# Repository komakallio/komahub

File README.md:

KomaHub Remote Power Switch and Sensor Platform
===============================================

Contents
--------

**EDA** - schematics and board layout, made in Eagle

**case** - STL files for a 3D-printed case

**software** - KomaHub control software

**firmware** - Firmware code

**tools** - tools for operating the KomaHub

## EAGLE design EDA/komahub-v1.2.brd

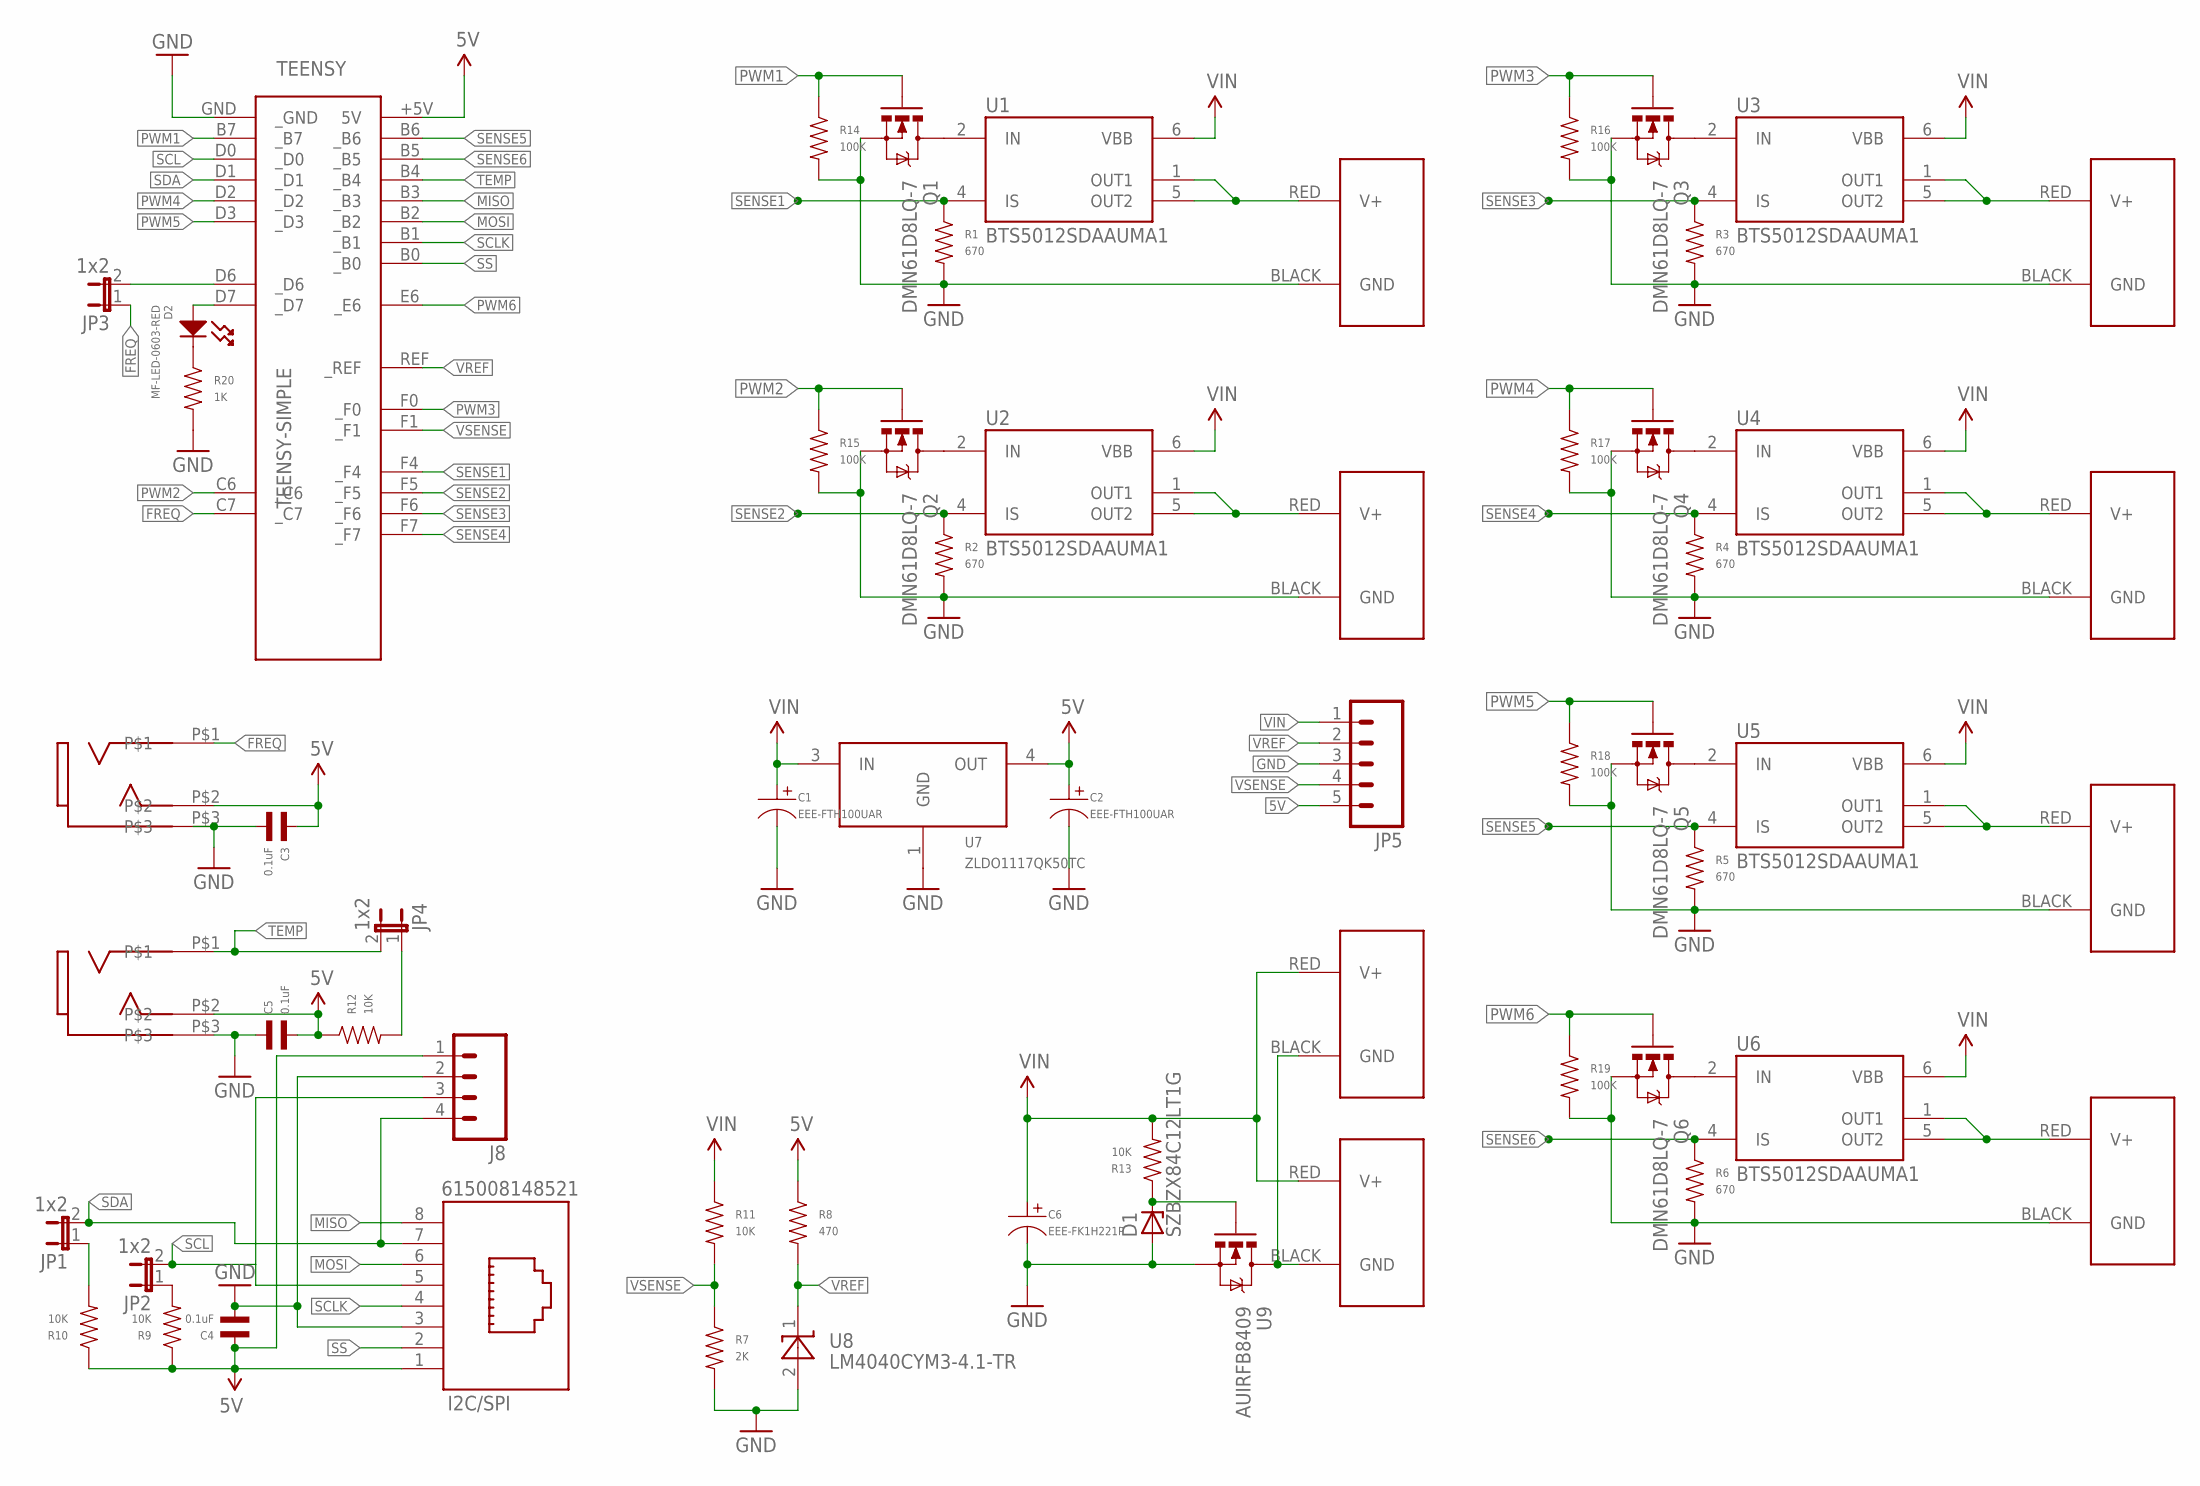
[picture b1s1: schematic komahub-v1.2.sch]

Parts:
C1, C2: EEE-FTH100UAR; CP4MM; MPN MF-CAP-4MM-10uF
C3, C4, C5: 0.1uF; C0603
C6: EEE-FK1H221P; CP10MM; MPN EEE-FT1H221AP
D1: SZBZX84C12LT1G; SOT23
D2: MF-LED-0603-RED; LED0603
FREQ: 35RASMT2BHNTRX
I2C/SPI: 615008148521
J1, J2, J6, J7: POWERPOLE_POWER25A_HORIZONTAL_G11; POWERPOLE_PAIR_25A_HORIZ_G11
J3, J4, J5, J9: POWERPOLE_POWER25A_HORIZONTAL_G12; POWERPOLE_PAIR_25A_HORIZ_G12
J8: M04PTH; 1X04
JP1, JP2, JP3, JP4: 1x2; 1X02
JP5: M05PTH; 1X05
Q1, Q2, Q3, Q4, Q5, Q6: DMN61D8LQ-7; SOT23-3
R1, R2, R3, R4, R5, R6: 670; R0603; MPN CR0603-FX-6800ELF
R7: 2K; R0603; MPN MF-RES-0603-2K
R8: 470; R0603; MPN MF-RES-0603-470
R9, R10, R11, R12, R13: 10K; R0603; MPN MF-RES-0603-10K
R14, R15, R16, R17, R18, R19: 100K; R0603; MPN MF-RES-0603-2K
R20: 1K; R0603
TEENSY: TEENSY-SIMPLE
TEMP: 35RASMT2BHNTRX
U1, U2, U3, U4, U5, U6: BTS5012SDAAUMA1; TO114P998X235-5_6N
U7: ZLDO1117QK50TC; DPAK
U8: LM4040CYM3-4.1-TR; SOT-23
U9: AUIRFB8409; TO220AV

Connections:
5V: C2.P$1, C3.P$1, C4.P$1, C5.P$2, FREQ.P$2, I2C/SPI.1 (8), J8.1, JP5.5, R8.P$1, R9.P$1, R10.P$1, R12.P$1, TEENSY.+5V (5V), TEMP.P$2, U7.4 (OUT)
FREQ: FREQ.P$1, JP3.1, TEENSY.C7 (_C7)
GND: C1.P$2, C2.P$2, C3.P$2, C4.P$2, C5.P$1, C6.P$2, D1.1 (A), FREQ.P$3, I2C/SPI.3 (6), J1.BLACK (GND), J2.BLACK (GND), J3.BLACK (GND), J5.BLACK (GND), J7.BLACK (GND), J8.2, J9.BLACK (GND), JP5.3, Q1.2 (S), Q2.2 (S), Q3.2 (S), Q4.2 (S), Q5.2 (S), Q6.2 (S), R1.P$2, R2.P$2, R3.P$2, R4.P$2, R5.P$2, R6.P$2, R7.P$2, R14.P$2, R15.P$2, R16.P$2, R17.P$2, R18.P$2, R19.P$2, R20.P$2, TEENSY.GND (_GND), TEMP.P$3, U7.1 (GND), U8.2 (A), U9.3 (S)
GNDIN: J4.BLACK (GND), J6.BLACK (GND), U9.2 (D)
MISO: I2C/SPI.8 (1), TEENSY.B3 (_B3)
MOSI: I2C/SPI.6 (3), TEENSY.B2 (_B2)
unnamed: JP3.2, TEENSY.D6 (_D6)
unnamed: JP2.1, R9.P$2
unnamed: JP4.1, R12.P$2
unnamed: JP1.1, R10.P$2
unnamed: D1.3 (C), R13.P$1, U9.1 (G)
unnamed: D2.CATHODE, R20.P$1
unnamed: D2.ANODE, TEENSY.D7 (_D7)
PWM1: Q1.1 (G), R14.P$1, TEENSY.B7 (_B7)
PWM2: Q2.1 (G), R15.P$1, TEENSY.C6 (_C6)
PWM3: Q3.1 (G), R16.P$1, TEENSY.F0 (_F0)
PWM4: Q4.1 (G), R17.P$1, TEENSY.D2 (_D2)
PWM5: Q5.1 (G), R18.P$1, TEENSY.D3 (_D3)
PWM6: Q6.1 (G), R19.P$1, TEENSY.E6 (_E6)
PWMT1: Q1.3 (D), U1.2 (IN)
PWMT2: Q2.3 (D), U2.2 (IN)
PWMT3: Q3.3 (D), U3.2 (IN)
PWMT4: Q4.3 (D), U4.2 (IN)
PWMT5: Q5.3 (D), U5.2 (IN)
PWMT6: Q6.3 (D), U6.2 (IN)
PWR1: J2.RED (V+), U1.1 (OUT1), U1.5 (OUT2)
PWR2: J3.RED (V+), U2.1 (OUT1), U2.5 (OUT2)
PWR3: J1.RED (V+), U3.1 (OUT1), U3.5 (OUT2)
PWR4: J5.RED (V+), U4.1 (OUT1), U4.5 (OUT2)
PWR5: J7.RED (V+), U5.1 (OUT1), U5.5 (OUT2)
PWR6: J9.RED (V+), U6.1 (OUT1), U6.5 (OUT2)
SCL: I2C/SPI.5 (4), J8.3, JP2.2, TEENSY.D0 (_D0)
SCLK: I2C/SPI.4 (5), TEENSY.B1 (_B1)
SDA: I2C/SPI.7 (2), J8.4, JP1.2, TEENSY.D1 (_D1)
SENSE1: R1.P$1, TEENSY.F4 (_F4), U1.4 (IS)
SENSE2: R2.P$1, TEENSY.F5 (_F5), U2.4 (IS)
SENSE3: R3.P$1, TEENSY.F6 (_F6), U3.4 (IS)
SENSE4: R4.P$1, TEENSY.F7 (_F7), U4.4 (IS)
SENSE5: R5.P$1, TEENSY.B6 (_B6), U5.4 (IS)
SENSE6: R6.P$1, TEENSY.B5 (_B5), U6.4 (IS)
SS: I2C/SPI.2 (7), TEENSY.B0 (_B0)
TEMP: JP4.2, TEENSY.B4 (_B4), TEMP.P$1
VIN: C1.P$1, C6.P$1, J4.RED (V+), J6.RED (V+), JP5.1, R11.P$1, R13.P$2, U1.6 (VBB), U2.6 (VBB), U3.6 (VBB), U4.6 (VBB), U5.6 (VBB), U6.6 (VBB), U7.3 (IN)
VREF: JP5.2, R8.P$2, TEENSY.REF (_REF), U8.1 (C)
VSENSE: JP5.4, R7.P$1, R11.P$2, TEENSY.F1 (_F1)

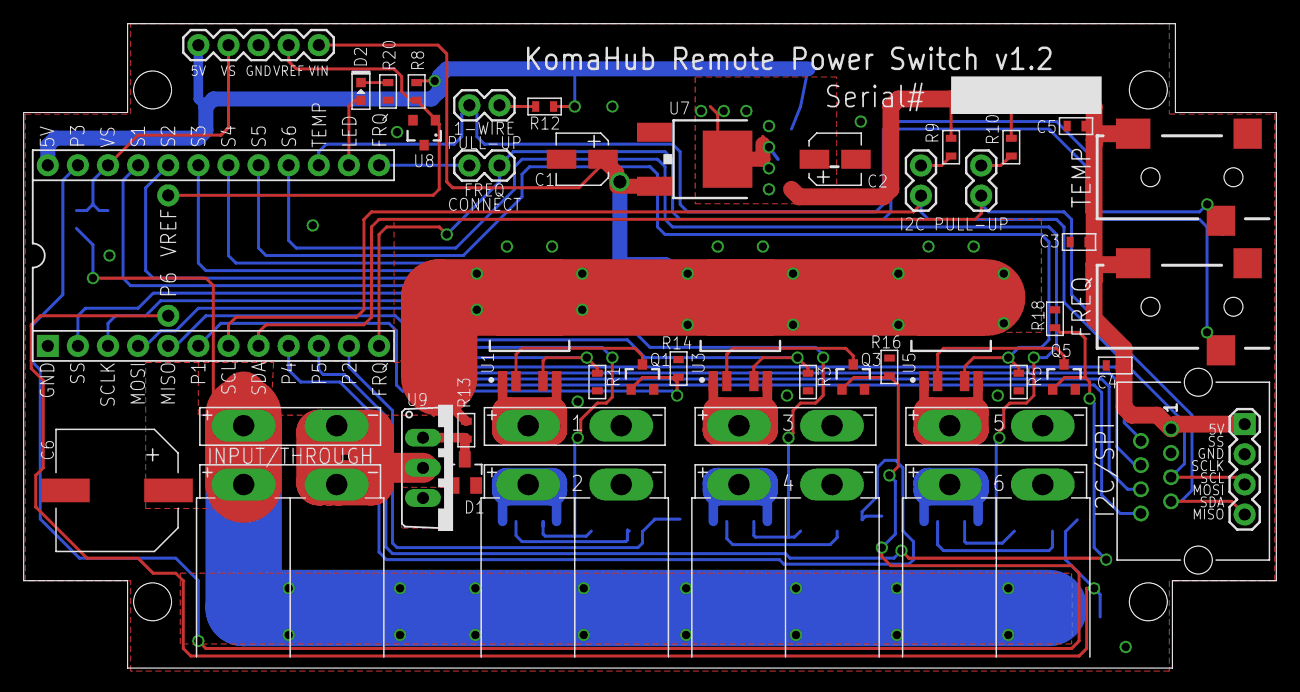
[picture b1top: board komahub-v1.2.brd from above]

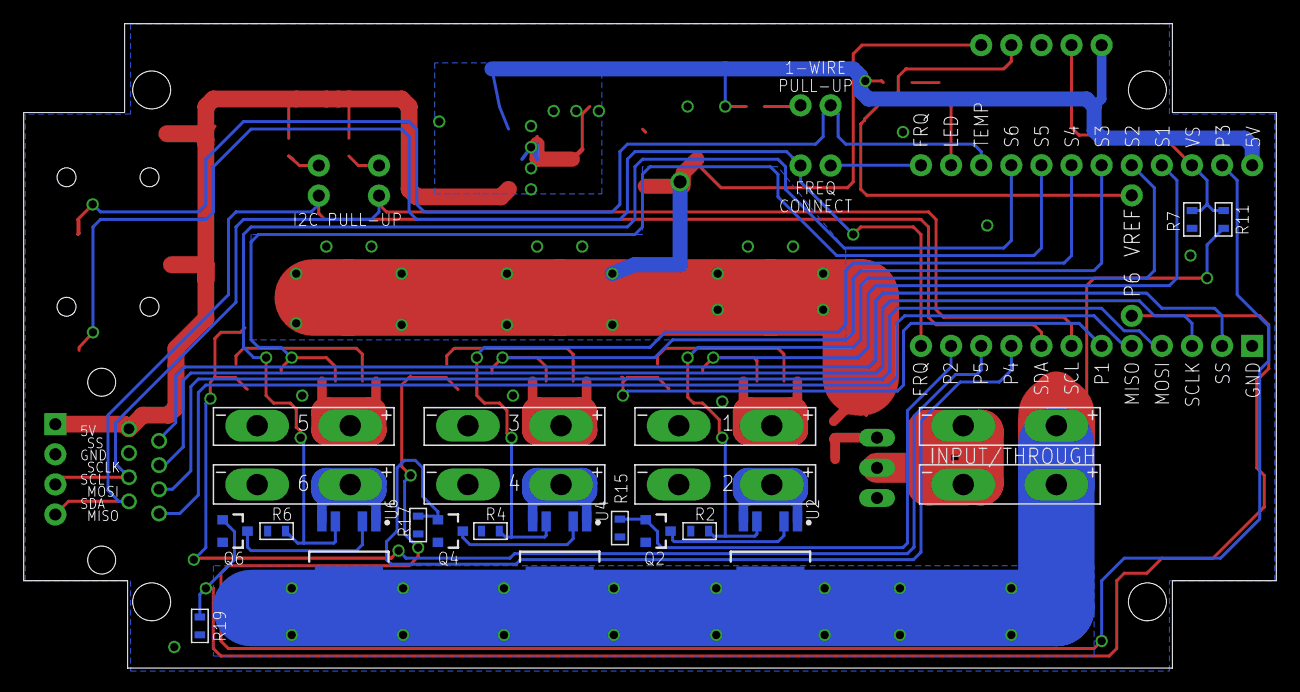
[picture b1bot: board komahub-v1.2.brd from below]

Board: 2 copper layers, 105.7 x 54.4 mm, 61 parts (14 on the bottom side), 45 nets.

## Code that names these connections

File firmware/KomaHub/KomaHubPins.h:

/*
 * Copyright (c) 2016 Jari Saukkonen
 *
 * Permission is hereby granted, free of charge, to any person obtaining
 * a copy of this software and associated documentation files (the
 * "Software"), to deal in the Software without restriction, including
 * without limitation the rights to use, copy, modify, merge, publish,
 * distribute, sublicense, and/or sell copies of the Software, and to
 * permit persons to whom the Software is furnished to do so, subject to
 * the following conditions:
 *
 * The above copyright notice and this permission notice shall be included
 * in all copies or substantial portions of the Software.
 *
 * THE SOFTWARE IS PROVIDED "AS IS", WITHOUT WARRANTY OF ANY KIND,
 * EXPRESS OR IMPLIED, INCLUDING BUT NOT LIMITED TO THE WARRANTIES OF
 * MERCHANTABILITY, FITNESS FOR A PARTICULAR PURPOSE AND NONINFRINGEMENT.
 * IN NO EVENT SHALL THE AUTHORS OR COPYRIGHT HOLDERS BE LIABLE FOR ANY
 * CLAIM, DAMAGES OR OTHER LIABILITY, WHETHER IN AN ACTION OF CONTRACT,
 * TORT OR OTHERWISE, ARISING FROM, OUT OF OR IN CONNECTION WITH THE
 * SOFTWARE OR THE USE OR OTHER DEALINGS IN THE SOFTWARE.
 */

#ifndef KOMAHUBPINS_H
#define KOMAHUBPINS_H

#include <Arduino.h>

namespace KomaHub {

enum Pin {
    SS = 0, 
    SCLK = 1, 
    MOSI = 2, 
    MISO = 3,
    SCL = 5, 
    SDA = 6,
    VSENSE = A1,
    SENSE1 = A2, 
    SENSE2 = A3, 
    SENSE3 = A4, 
    SENSE4 = A5, 
    SENSE5 = A6, 
    SENSE6 = A7,
    P1 = 4, 
    P2 = 9, 
    P3 = 21, 
    P4 = 7, 
    P5 = 8, 
    P6 = 24,
    AUX1 = 9,
    AUX1_2 = 11,
    AUX2 = 13,
    LED = 12
};

}

#endif

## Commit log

2017-01-25 Initial revision
2017-01-25 Add readme
2017-01-25 Add LICENSE
2017-01-25 Fix multiple commands in one packet
2017-02-11 Add utility for querying komahub state
2017-02-11 Fix endianness
2017-02-11 Avoid error message for commands that do not send responses
2017-02-11 Initial implementation for reading voltage and sense current
2017-02-12 Fix interrupt-driven ADC sampling
2017-02-12 Remove LED debugging code
2017-02-15 Implement fuse handling, fix eeprom handling to persist state, add serial debug mode
2017-02-15 Fix reading the serial number
2017-09-07 Use platformio as the build system
2017-09-07 Remove extra directory
2017-09-20 Update tools to work with current komahub
2017-09-20 Komahub Windows UI, work-in-progress
2017-09-20 Remove user-specific config files.
2017-09-20 Add user-specific Visual Studio files to gitignore.
2017-09-27 Use a custom dll based on PJRC raw hid code for communication
2017-09-27 Refactor data types to separate class; start implementing settings and UI functionality
2017-09-27 Make a more sensible split between factory settings, output settings and runtime status
2017-09-28 Use table layout in main form; more communication with device
2017-09-28 Fix GetOutputCommand
2017-09-28 We should probably reserve space for additional output data
2017-09-30 Make things (UI sync with hardware, PWM, etc) work
2017-09-30 Simplify command protocol by removing command length. Fix bugs in GetOutputCommand and struct padding
2017-10-02 Pack EEPROM data structures tightly
2017-10-02 Support updating factory config data
2017-10-02 Add commands for updating some factory configuration data and rebooting to bootloader for firmware updates
2017-10-03 Reorganize power output / input voltage parsing; get rid of ringbuffer in AnalogInput and calculate average values in sync relative to the pwm cycle
2017-10-03 Initialize fuse delay and sky quality default value
2017-10-03 Implement fuse reset
2017-10-07 First shot at measuring power output calibration data
2017-10-07 Update hidsend/factoryreset to work with latest firmware
2017-10-09 Measure and produce output calibration data; does not yet upload calibration coefficients to komahub
2017-10-10 Raise error if calibration coefficients are out of range
2017-10-10 Better approximation of true power output using a second-order function and external calibration
2017-10-10 Formatting fixes
2017-10-10 Send power output calibration data to KomaHub
2017-10-11 update gitignore
2017-10-11 Use real calibration coefficients in factory reset
2017-10-11 Add get power usage -command
2017-10-11 Fix overflow in initialization
2017-10-11 Fix rebooting to bootloader
2017-10-11 Fix power output and input voltage calculations
2017-10-13 Document EEPROM layout
2017-10-13 Store board revision to EEPROM so that we are able to support multiple board revisions with the same firmware code
2017-10-13 Support slower than instant fuses; collect power usage data into a cyclical history buffer to be able to slow down fuse tripping
2017-10-14 Fix compilation
2017-10-14 Describe status response message format as a struct
2017-10-14 Fix formatting
2017-10-14 Skeleton code for sky temperature measurement
2017-10-14 Implement handling for external sensors
2017-10-14 Rename SQM->SkyQuality
2017-10-15 Document USB responses as structs, clean up USB handling
2017-10-26 Fix binary logic when manipulating relay open / fuse triggered fields
2017-10-26 fix typo
2017-10-26 initialize output to default settings when calibrating
2017-10-26 fix serial number endianness
2017-10-26 script for booting komahub to bootloader mode
2017-10-27 Fix buffer overflow
2017-10-27 Turn output off at the end of a calibration run
2017-11-09 Add error handling and error dialog for USB comms
2017-11-09 Remove unnecessary settings
2017-11-09 Add cute icon for the app
2017-11-09 Disable UI updates when data is updated from the device
2018-05-07 remove extra import
2018-05-07 fix gitignore
2018-05-08 Fix boot loader entry
2018-05-08 Scale temperature values properly
2018-05-08 Display all data from status messages
2018-05-08 Use DS1620 as an external temperature sensor
2018-05-08 Disable unused features
2018-07-16 Read temperature sensor data from response
2018-07-16 Display primary and secondary mirror temperatures
2018-07-16 If KomaHub is already running, activate the already-running instance
2018-07-18 Support toggling outputs via a simple REST api
2018-07-30 Add support for board version specific functionality. Make power measurement divisor different for 1.0 / 1.1 boards.
2018-07-30 Fix include style
2018-07-30 Verify that the output can turn itself off at the end of calibration run
2018-09-18 Support hardware revisioning inside the same firmware code
2018-09-22 Fix firmware version
2018-09-22 Add STL files for case
2018-09-28 Set theme jekyll-theme-cayman
2018-09-30 Add connector documentation image
2018-10-21 Add screenshot to repo
2018-10-21 Update docs config for local testing
2018-10-21 Update main GH page
2018-10-21 Add Finnish manual page
2018-10-25 Better error handling to device detection
2018-10-25 Include msvc runtime + installer
2018-10-25 Get rid of unused settings for release
2018-10-25 Link to downloads
2018-10-31 Add schematics for board rev 1.2
2018-10-31 Get rid of feature flags and actually detect sensors; add sensor present data to status output
2018-10-31 Fix AUX1 pin assignment
2018-11-03 Support MLX90614 sensor for sensing sky temperature
2018-11-03 Support sky quality estimation with TLS237 light-frequency converter
2018-11-03 Bump firmware version to 1.2
2018-11-03 Show firmware major / minor version in the correct order
2018-11-03 Read and display sensor data
2018-11-03 Display dew point and second external temperature in control application
2018-11-03 Add /sensors query to REST api
2018-11-03 Describe sensor usage in the manual
2018-11-04 Add VS Code files to gitignore
2018-11-04 Add empty WPF window to project
2018-11-04 Add static content to WPF GUI
2018-11-04 Replace WinForms GUI with WPF
2018-11-05 äElaborate sensor descriptions on required pull-up resistors
2018-11-06 ASCOM ObservingConditions driver
2018-11-06 Fix setup script and solution directories
2019-07-20 Update to newer PlatformIO; document build process
2019-07-20 Implement PWM_FAN output type
2019-07-20 Fix code style
2019-07-20 First implementation of automatic dew controller
2019-07-26 More simple heating control without PID and automatic fan control
2019-07-26 Script for updating settings data
2019-08-03 Use hardware PWM for fan control
2019-08-10 Don't make backward incompatible change
2019-11-02 Bump nokogiri from 1.8.5 to 1.10.5 in /docs
    Bumps [nokogiri](https://github.com/sparklemotion/nokogiri) from 1.8.5 to 1.10.5.
    - [Release notes](https://github.com/sparklemotion/nokogiri/releases)
    - [Changelog](https://github.com/sparklemotion/nokogiri/blob/master/CHANGELOG.md)
    - [Commits](https://github.com/sparklemotion/nokogiri/compare/v1.8.5...v1.10.5)
2020-02-25 Bump nokogiri from 1.8.5 to 1.10.8 in /docs
    Bumps [nokogiri](https://github.com/sparklemotion/nokogiri) from 1.8.5 to 1.10.8.
    - [Release notes](https://github.com/sparklemotion/nokogiri/releases)
    - [Changelog](https://github.com/sparklemotion/nokogiri/blob/master/CHANGELOG.md)
    - [Commits](https://github.com/sparklemotion/nokogiri/compare/v1.8.5...v1.10.8)
2021-05-19 Bump nokogiri from 1.8.5 to 1.11.4 in /docs
    Bumps [nokogiri](https://github.com/sparklemotion/nokogiri) from 1.8.5 to 1.11.4.
    - [Release notes](https://github.com/sparklemotion/nokogiri/releases)
    - [Changelog](https://github.com/sparklemotion/nokogiri/blob/main/CHANGELOG.md)
    - [Commits](https://github.com/sparklemotion/nokogiri/compare/v1.8.5...v1.11.4)
2021-07-13 Bump addressable from 2.5.2 to 2.8.0 in /docs
    Bumps [addressable](https://github.com/sporkmonger/addressable) from 2.5.2 to 2.8.0.
    - [Release notes](https://github.com/sporkmonger/addressable/releases)
    - [Changelog](https://github.com/sporkmonger/addressable/blob/main/CHANGELOG.md)
    - [Commits](https://github.com/sporkmonger/addressable/compare/addressable-2.5.2...addressable-2.8.0)
    ---
    updated-dependencies:
2021-09-27 Bump nokogiri from 1.8.5 to 1.12.5 in /docs
    Bumps [nokogiri](https://github.com/sparklemotion/nokogiri) from 1.8.5 to 1.12.5.
    - [Release notes](https://github.com/sparklemotion/nokogiri/releases)
    - [Changelog](https://github.com/sparklemotion/nokogiri/blob/main/CHANGELOG.md)
    - [Commits](https://github.com/sparklemotion/nokogiri/compare/v1.8.5...v1.12.5)
    ---
    updated-dependencies:
2022-04-12 Bump nokogiri from 1.8.5 to 1.13.4 in /docs
    Bumps [nokogiri](https://github.com/sparklemotion/nokogiri) from 1.8.5 to 1.13.4.
    - [Release notes](https://github.com/sparklemotion/nokogiri/releases)
    - [Changelog](https://github.com/sparklemotion/nokogiri/blob/v1.13.4/CHANGELOG.md)
    - [Commits](https://github.com/sparklemotion/nokogiri/compare/v1.8.5...v1.13.4)
    ---
    updated-dependencies:
2022-05-18 Bump nokogiri from 1.8.5 to 1.13.6 in /docs
    Bumps [nokogiri](https://github.com/sparklemotion/nokogiri) from 1.8.5 to 1.13.6.
    - [Release notes](https://github.com/sparklemotion/nokogiri/releases)
    - [Changelog](https://github.com/sparklemotion/nokogiri/blob/main/CHANGELOG.md)
    - [Commits](https://github.com/sparklemotion/nokogiri/compare/v1.8.5...v1.13.6)
    ---
    updated-dependencies:
2022-06-22 Bump Newtonsoft.Json from 11.0.2 to 13.0.1 in /software/KomaHub/KomaHub
    Bumps [Newtonsoft.Json](https://github.com/JamesNK/Newtonsoft.Json) from 11.0.2 to 13.0.1.
    - [Release notes](https://github.com/JamesNK/Newtonsoft.Json/releases)
    - [Commits](https://github.com/JamesNK/Newtonsoft.Json/compare/11.0.2...13.0.1)
    ---
    updated-dependencies:
    - dependency-name: Newtonsoft.Json
2022-06-22 Bump Newtonsoft.Json in /software/ASCOMObservingConditions
    Bumps [Newtonsoft.Json](https://github.com/JamesNK/Newtonsoft.Json) from 11.0.2 to 13.0.1.
    - [Release notes](https://github.com/JamesNK/Newtonsoft.Json/releases)
    - [Commits](https://github.com/JamesNK/Newtonsoft.Json/compare/11.0.2...13.0.1)
    ---
    updated-dependencies:
    - dependency-name: Newtonsoft.Json
2022-07-22 Bump tzinfo from 1.2.5 to 1.2.10 in /docs
    Bumps [tzinfo](https://github.com/tzinfo/tzinfo) from 1.2.5 to 1.2.10.
    - [Release notes](https://github.com/tzinfo/tzinfo/releases)
    - [Changelog](https://github.com/tzinfo/tzinfo/blob/master/CHANGES.md)
    - [Commits](https://github.com/tzinfo/tzinfo/compare/v1.2.5...v1.2.10)
    ---
    updated-dependencies:
2022-08-16 Fix typo in manual
2022-08-16 Fix curl syntax
2022-10-06 Bump addressable from 2.5.2 to 2.8.1 in /docs
    Bumps [addressable](https://github.com/sporkmonger/addressable) from 2.5.2 to 2.8.1.
    - [Release notes](https://github.com/sporkmonger/addressable/releases)
    - [Changelog](https://github.com/sporkmonger/addressable/blob/main/CHANGELOG.md)
    - [Commits](https://github.com/sporkmonger/addressable/compare/addressable-2.5.2...addressable-2.8.1)
    ---
    updated-dependencies:
2022-12-08 Bump Newtonsoft.Json from 11.0.2 to 13.0.2 in /software/KomaHub/KomaHub
    Bumps [Newtonsoft.Json](https://github.com/JamesNK/Newtonsoft.Json) from 11.0.2 to 13.0.2.
    - [Release notes](https://github.com/JamesNK/Newtonsoft.Json/releases)
    - [Commits](https://github.com/JamesNK/Newtonsoft.Json/compare/11.0.2...13.0.2)
    ---
    updated-dependencies:
    - dependency-name: Newtonsoft.Json
2022-12-08 Bump Newtonsoft.Json in /software/ASCOMObservingConditions
    Bumps [Newtonsoft.Json](https://github.com/JamesNK/Newtonsoft.Json) from 11.0.2 to 13.0.2.
    - [Release notes](https://github.com/JamesNK/Newtonsoft.Json/releases)
    - [Commits](https://github.com/JamesNK/Newtonsoft.Json/compare/11.0.2...13.0.2)
    ---
    updated-dependencies:
    - dependency-name: Newtonsoft.Json

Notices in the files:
parts and their libraries:
SparkFun-DiscreteSemi: Licensing: Creative Commons ShareAlike 4.0 International - https://creativecommons.org/licenses/by-sa/4.0
EAGLE-INPUT_OUTPUT_CONNECTORS-rev17a: Copyright: Würth Elektronik
teensy: Licensed Under Creative Commons Attribution-ShareAlike 3.0 Unported (CC BY-SA 3.0)
